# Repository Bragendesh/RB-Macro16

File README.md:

# RB-Macro16
A basic 16-key macropad with an optional spot for a rotary encoder and per-key RGB backlighting

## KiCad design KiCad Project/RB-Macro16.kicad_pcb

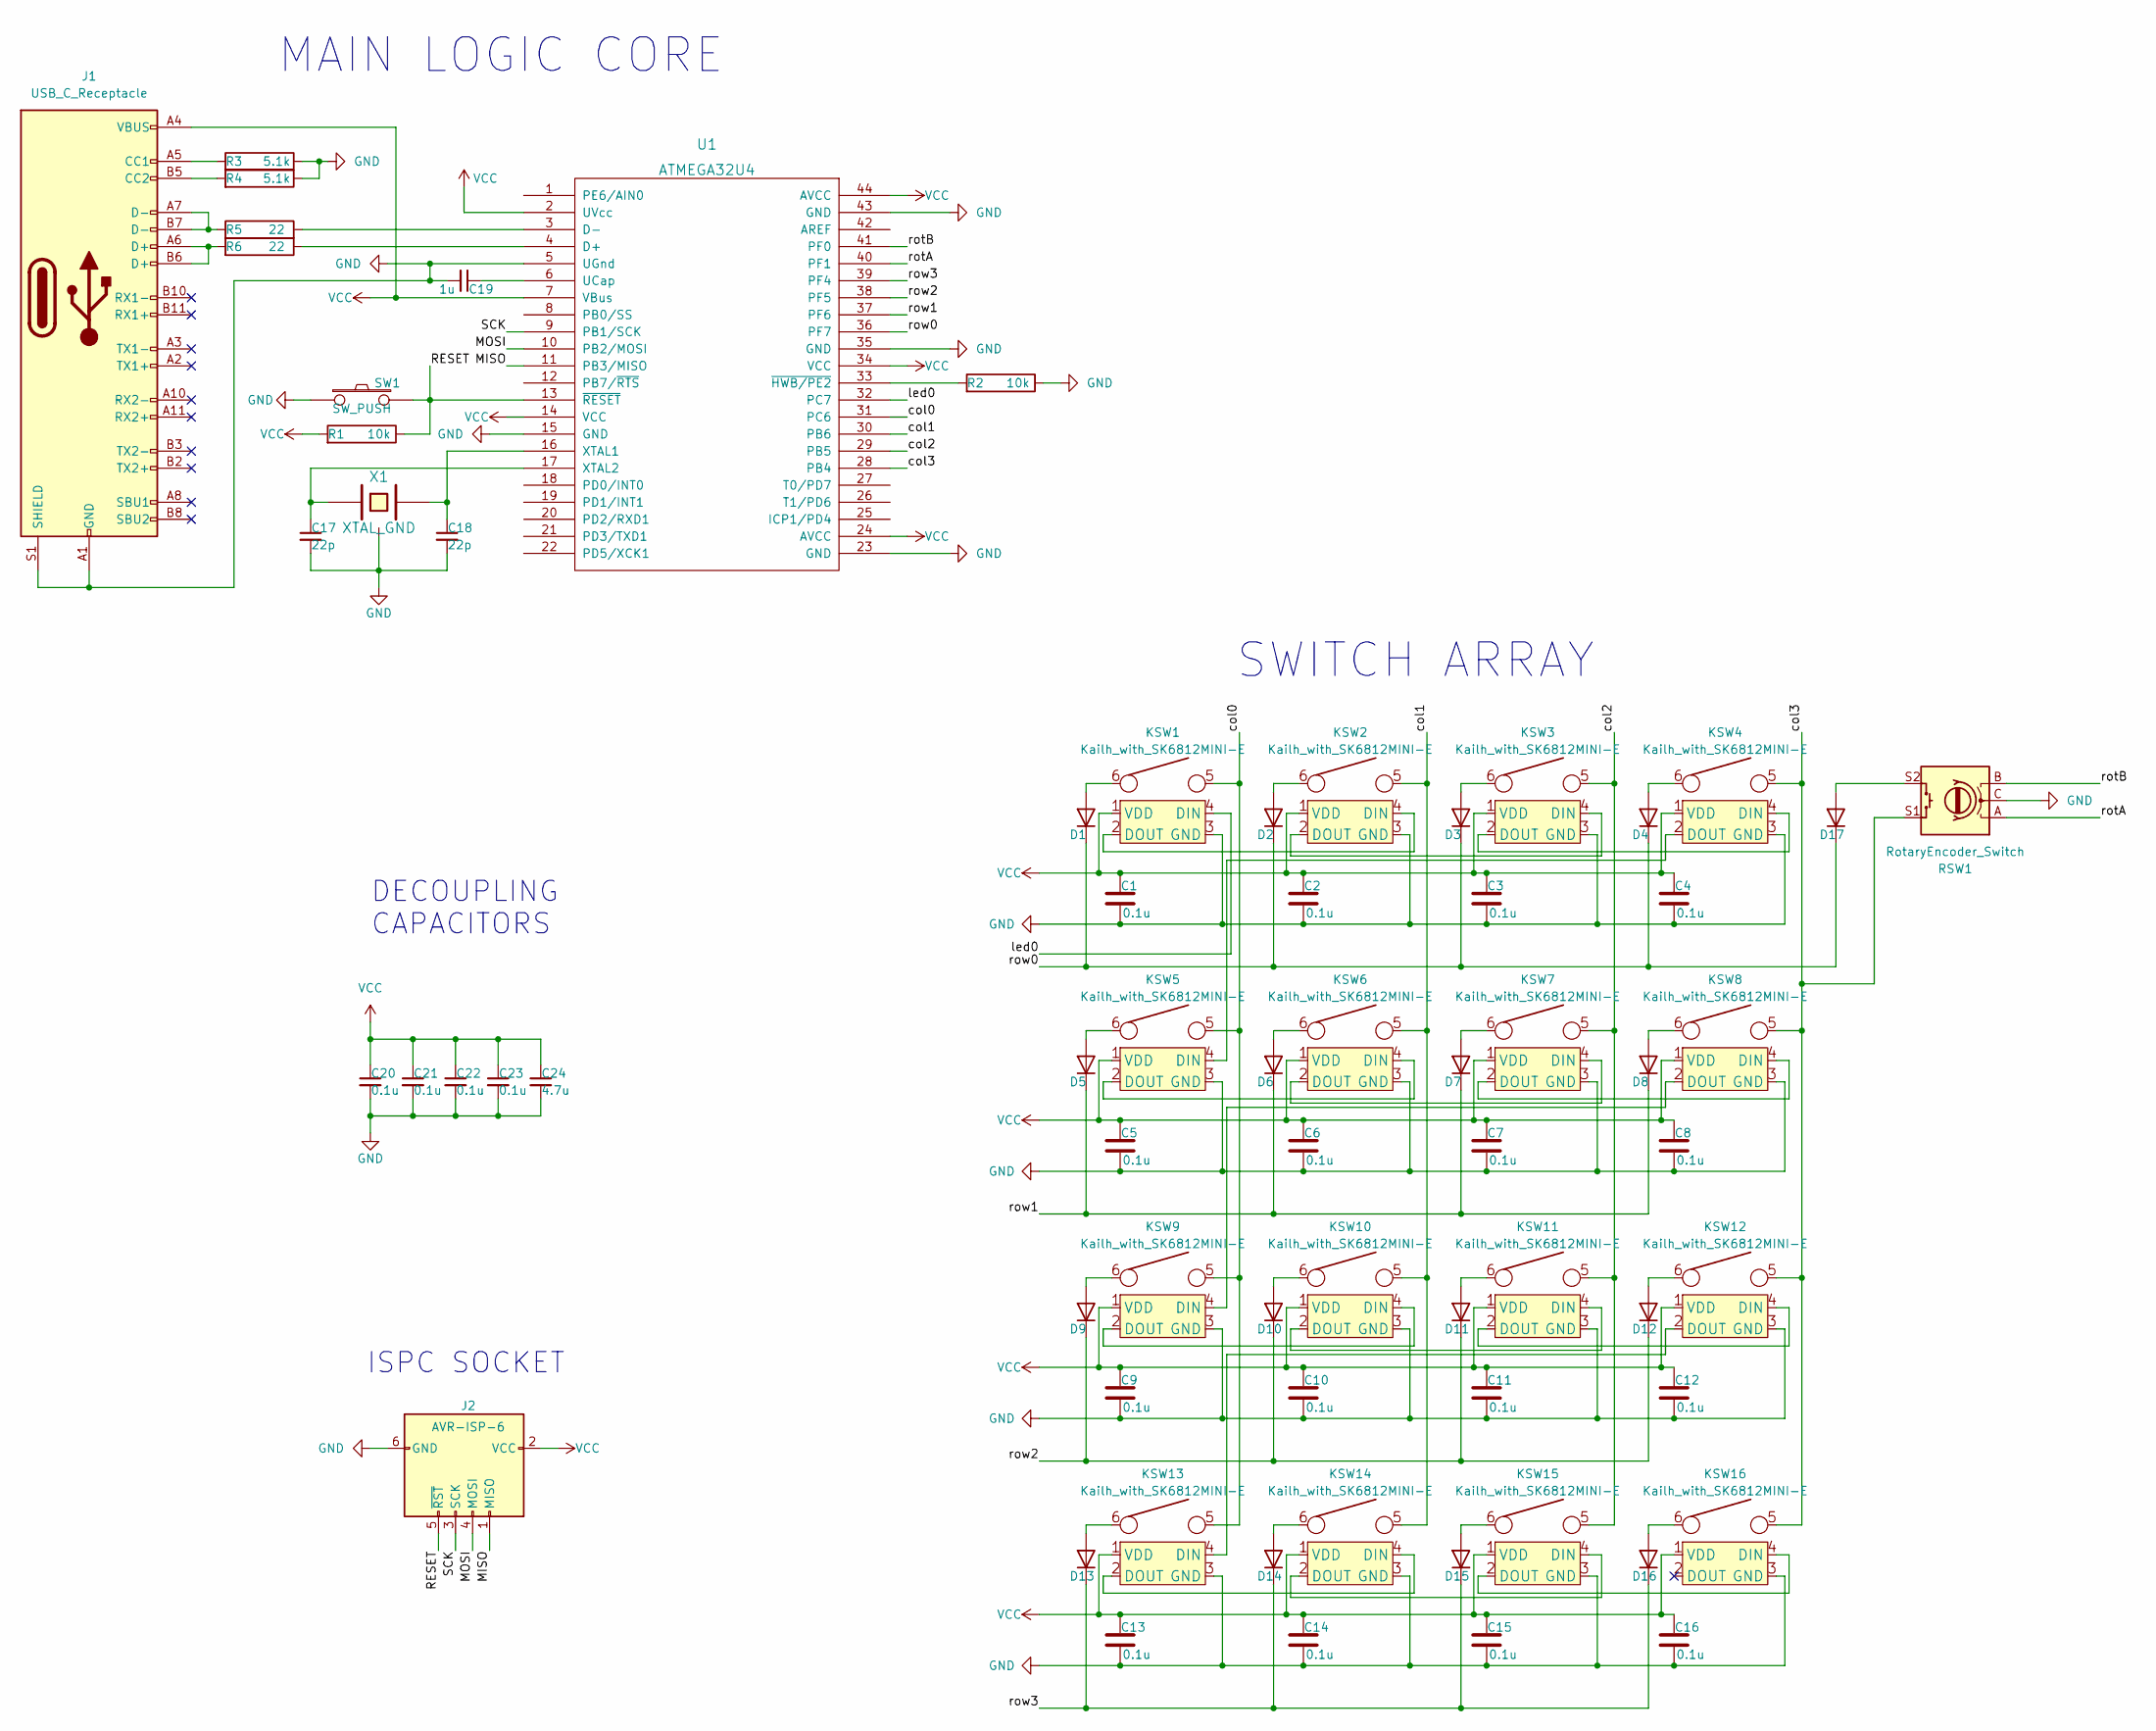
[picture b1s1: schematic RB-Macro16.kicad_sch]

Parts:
C1, C2, C3, C4, C5, C6, C7, C8, C9, C10, C11, C12, C13, C14, C15, C16, C20, C21, C22, C23: 0.1u; C_0805_2012Metric_Pad1.18x1.45mm_HandSolder
C17, C18: 22p; C_0805_2012Metric_Pad1.18x1.45mm_HandSolder
C19: 1u; C_0805_2012Metric_Pad1.18x1.45mm_HandSolder
C24: 4.7u; C_0805_2012Metric_Pad1.18x1.45mm_HandSolder
D1, D2, D3, D4, D5, D6, D7, D8, D9, D10, D11, D12, D13, D14, D15, D16, D17: D; D_SOD-123
J1: USB_C_Receptacle; USB_C_Receptacle_Amphenol_12401610E4-2A
J2: AVR-ISP-6; AVR_ICSP_3x2
KSW1, KSW2, KSW3, KSW4, KSW5, KSW6, KSW7, KSW8, KSW9, KSW10, KSW11, KSW12, KSW13, KSW14, KSW15, KSW16: Kailh_with_SK6812MINI-E
R1, R2: 10k; R_Axial_DIN0207_L6.3mm_D2.5mm_P7.62mm_Horizontal
R3, R4: 5.1k; R_Axial_DIN0207_L6.3mm_D2.5mm_P7.62mm_Horizontal
R5, R6: 22; R_Axial_DIN0207_L6.3mm_D2.5mm_P7.62mm_Horizontal
RSW1: RotaryEncoder_Switch; RotaryEncoder_Alps_EC12E-Switch_Vertical_H20mm
SW1: SW_PUSH; SW_PUSH_6mm
U1: ATMEGA32U4; TQFP-44_10x10mm_P0.8mm
X1: XTAL_GND; Crystal_SMD_SeikoEpson_FA238-4Pin_3.2x2.5mm_HandSoldering

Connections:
/MISO: J2.1 (MISO), U1.11 (PB3/MISO)
/MOSI: J2.4 (MOSI), U1.10 (PB2/MOSI)
/RESET: J2.5 (~RST), R1.2, SW1.2, U1.13 (~RESET)
/SCK: J2.3 (SCK), U1.9 (PB1/SCK)
/col0: KSW1.5, KSW5.5, KSW9.5, KSW13.5, U1.31 (PC6)
/col1: KSW2.5, KSW6.5, KSW10.5, KSW14.5, U1.30 (PB6)
/col2: KSW3.5, KSW7.5, KSW11.5, KSW15.5, U1.29 (PB5)
/col3: KSW4.5, KSW8.5, KSW12.5, KSW16.5, RSW1.S1, U1.28 (PB4)
/led0: KSW1.4 (DIN), U1.32 (PC7)
/rotA: RSW1.A, U1.40 (PF1)
/rotB: RSW1.B, U1.41 (PF0)
/row0: D1.1 (K), D2.1 (K), D3.1 (K), D4.1 (K), D17.1 (K), U1.36 (PF7)
/row1: D5.1 (K), D6.1 (K), D7.1 (K), D8.1 (K), U1.37 (PF6)
/row2: D9.1 (K), D10.1 (K), D11.1 (K), D12.1 (K), U1.38 (PF5)
/row3: D13.1 (K), D14.1 (K), D15.1 (K), D16.1 (K), U1.39 (PF4)
GND: C1.2, C2.2, C3.2, C4.2, C5.2, C6.2, C7.2, C8.2, C9.2, C10.2, C11.2, C12.2, C13.2, C14.2, C15.2, C16.2, C17.2, C18.2, C19.2, C20.2, C21.2, C22.2, C23.2, C24.2, J1.A1 (GND), J1.A12 (GND), J1.B1 (GND), J1.B12 (GND), J1.S1 (SHIELD), J2.6 (GND), KSW1.3 (GND), KSW2.3 (GND), KSW3.3 (GND), KSW4.3 (GND), KSW5.3 (GND), KSW6.3 (GND), KSW7.3 (GND), KSW8.3 (GND), KSW9.3 (GND), KSW10.3 (GND), KSW11.3 (GND), KSW12.3 (GND), KSW13.3 (GND), KSW14.3 (GND), KSW15.3 (GND), KSW16.3 (GND), R2.2, R3.2, R4.2, RSW1.C, SW1.1, U1.5 (UGnd), U1.15 (GND), U1.23 (GND), U1.35 (GND), U1.43 (GND), X1.3
unnamed: D1.2 (A), KSW1.6
unnamed: D2.2 (A), KSW2.6
unnamed: D3.2 (A), KSW3.6
unnamed: D4.2 (A), KSW4.6
unnamed: D5.2 (A), KSW5.6
unnamed: D6.2 (A), KSW6.6
unnamed: D7.2 (A), KSW7.6
unnamed: D8.2 (A), KSW8.6
unnamed: D9.2 (A), KSW9.6
unnamed: D10.2 (A), KSW10.6
unnamed: D11.2 (A), KSW11.6
unnamed: D12.2 (A), KSW12.6
unnamed: D13.2 (A), KSW13.6
unnamed: D14.2 (A), KSW14.6
unnamed: D15.2 (A), KSW15.6
unnamed: D16.2 (A), KSW16.6
unnamed: D17.2 (A), RSW1.S2
unnamed: J1.A5 (CC1), R3.1
unnamed: J1.B5 (CC2), R4.1
unnamed: J1.A6 (D+), J1.B6 (D+), R6.1
unnamed: J1.A7 (D-), J1.B7 (D-), R5.1
unnamed: KSW1.2 (DOUT), KSW2.4 (DIN)
unnamed: KSW2.2 (DOUT), KSW3.4 (DIN)
unnamed: KSW3.2 (DOUT), KSW4.4 (DIN)
unnamed: KSW4.2 (DOUT), KSW5.4 (DIN)
unnamed: KSW5.2 (DOUT), KSW6.4 (DIN)
unnamed: KSW6.2 (DOUT), KSW7.4 (DIN)
unnamed: KSW7.2 (DOUT), KSW8.4 (DIN)
unnamed: KSW8.2 (DOUT), KSW9.4 (DIN)
unnamed: KSW9.2 (DOUT), KSW10.4 (DIN)
unnamed: KSW10.2 (DOUT), KSW11.4 (DIN)
unnamed: KSW11.2 (DOUT), KSW12.4 (DIN)
unnamed: KSW12.2 (DOUT), KSW13.4 (DIN)
unnamed: KSW13.2 (DOUT), KSW14.4 (DIN)
unnamed: KSW14.2 (DOUT), KSW15.4 (DIN)
unnamed: KSW15.2 (DOUT), KSW16.4 (DIN)
unnamed: R6.2, U1.4 (D+)
unnamed: R5.2, U1.3 (D-)
unnamed: C19.1, U1.6 (UCap)
unnamed: C18.1, U1.16 (XTAL1), X1.2
unnamed: C17.1, U1.17 (XTAL2), X1.1
unnamed: R2.1, U1.33 (~HWB/PE2)
VCC: C1.1, C2.1, C3.1, C4.1, C5.1, C6.1, C7.1, C8.1, C9.1, C10.1, C11.1, C12.1, C13.1, C14.1, C15.1, C16.1, C20.1, C21.1, C22.1, C23.1, C24.1, J1.A4 (VBUS), J1.A9 (VBUS), J1.B4 (VBUS), J1.B9 (VBUS), J2.2 (VCC), KSW1.1 (VDD), KSW2.1 (VDD), KSW3.1 (VDD), KSW4.1 (VDD), KSW5.1 (VDD), KSW6.1 (VDD), KSW7.1 (VDD), KSW8.1 (VDD), KSW9.1 (VDD), KSW10.1 (VDD), KSW11.1 (VDD), KSW12.1 (VDD), KSW13.1 (VDD), KSW14.1 (VDD), KSW15.1 (VDD), KSW16.1 (VDD), R1.1, U1.2 (UVcc), U1.7 (VBus), U1.14 (VCC), U1.24 (AVCC), U1.34 (VCC), U1.44 (AVCC)

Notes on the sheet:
MAIN LOGIC CORE
ISPC SOCKET
DECOUPLING CAPACITORS
SWITCH ARRAY

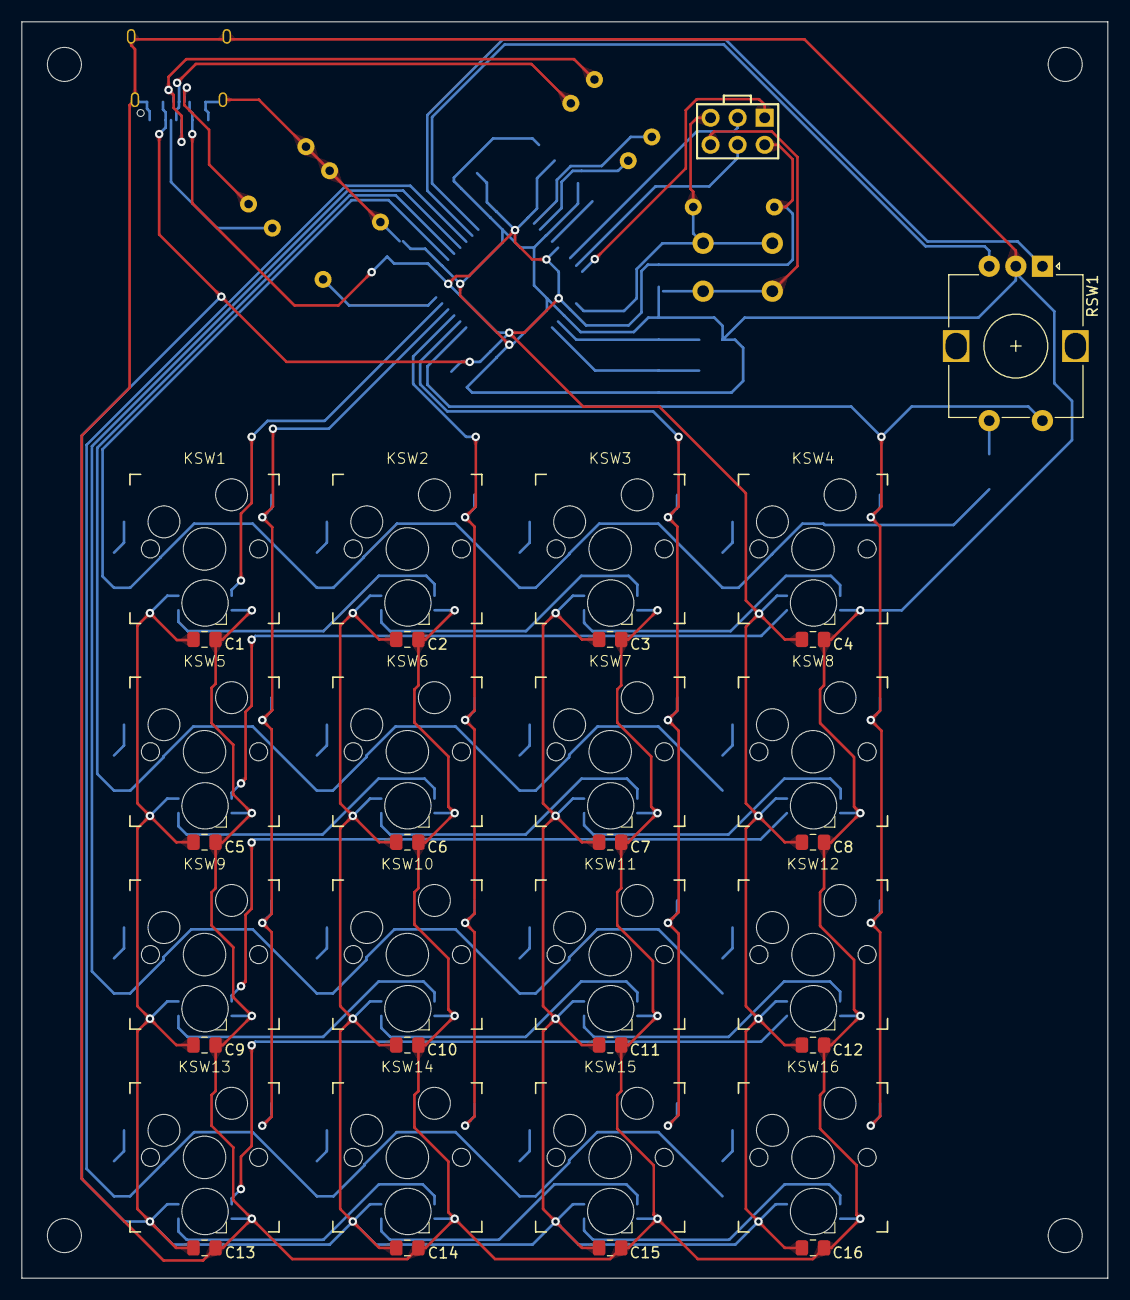
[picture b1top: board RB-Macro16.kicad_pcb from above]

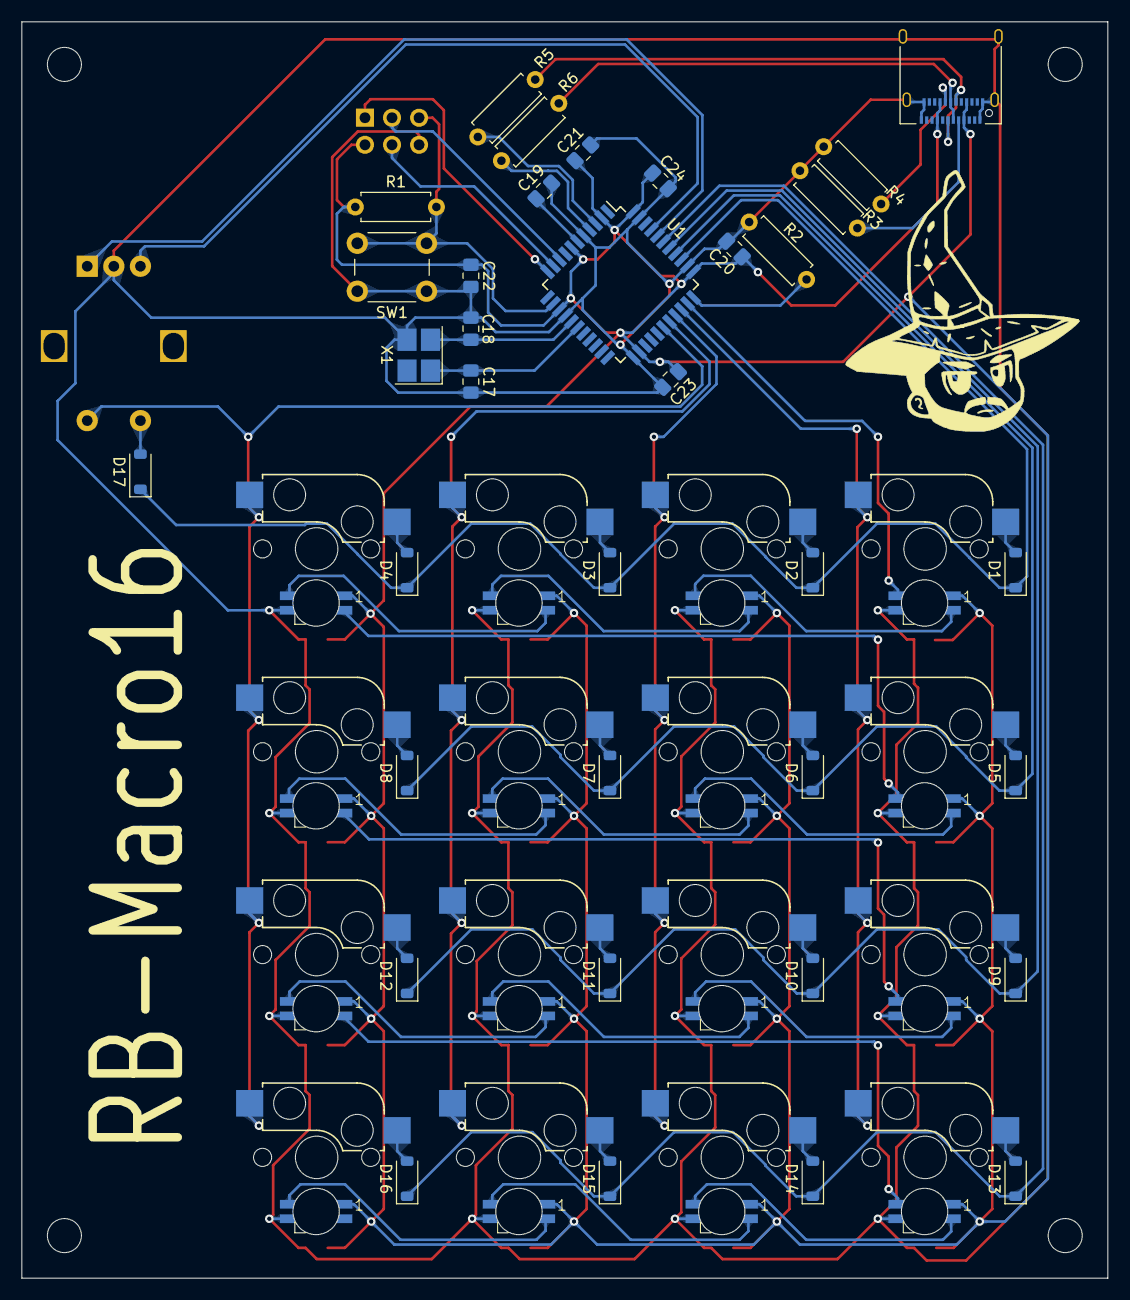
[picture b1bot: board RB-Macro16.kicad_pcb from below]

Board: 2 copper layers, 102.0 x 118.0 mm, 69 parts (35 on the bottom side), 59 nets.

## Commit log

2023-02-22 Schematic Design Initial
    Drew out the entire initial schematic including microcontroller, key switches, LEDs, and USB C receptacle.
2023-02-22 Finished Schematic
    Finished the schematic and associated all footprints to prep for PCB design
2023-02-22 New Switch Found
    Found a new MX Switch with LITEON LEDs
2023-02-22 Abandoned New Swtich
    Can't find LED new switch footprint uses. Began working on footprint for SK6812MINI-E from Adafruit as a replacement. Added capacitors to LED array and rebuilt it.
2023-02-23 New Switch Symbol and Footprint
    Redid switch symbol and footprint to combine hot swap footprint and reverse mount LED footprint. Started work on PCB, laying out switches, diodes, capacitors
2023-02-24 Routed PCB
    Routed most of the traces in the PCB for the switch block. uP in progress.
2023-02-24 Generated BOM
    BOM
2023-03-02 Placed ATMEGA
    Placed ATMEGA and XTAL and caps and routed traces to them
2023-03-08 Minor Changes
2023-03-08 Finished Traces
    Completed all traces
2023-03-09 Added Graphics and Finalized
    Added a graphic and finalized the design including integrity checks. Generated Gerber files.
